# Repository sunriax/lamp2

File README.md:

# WIFI controllable RGB LED lamp

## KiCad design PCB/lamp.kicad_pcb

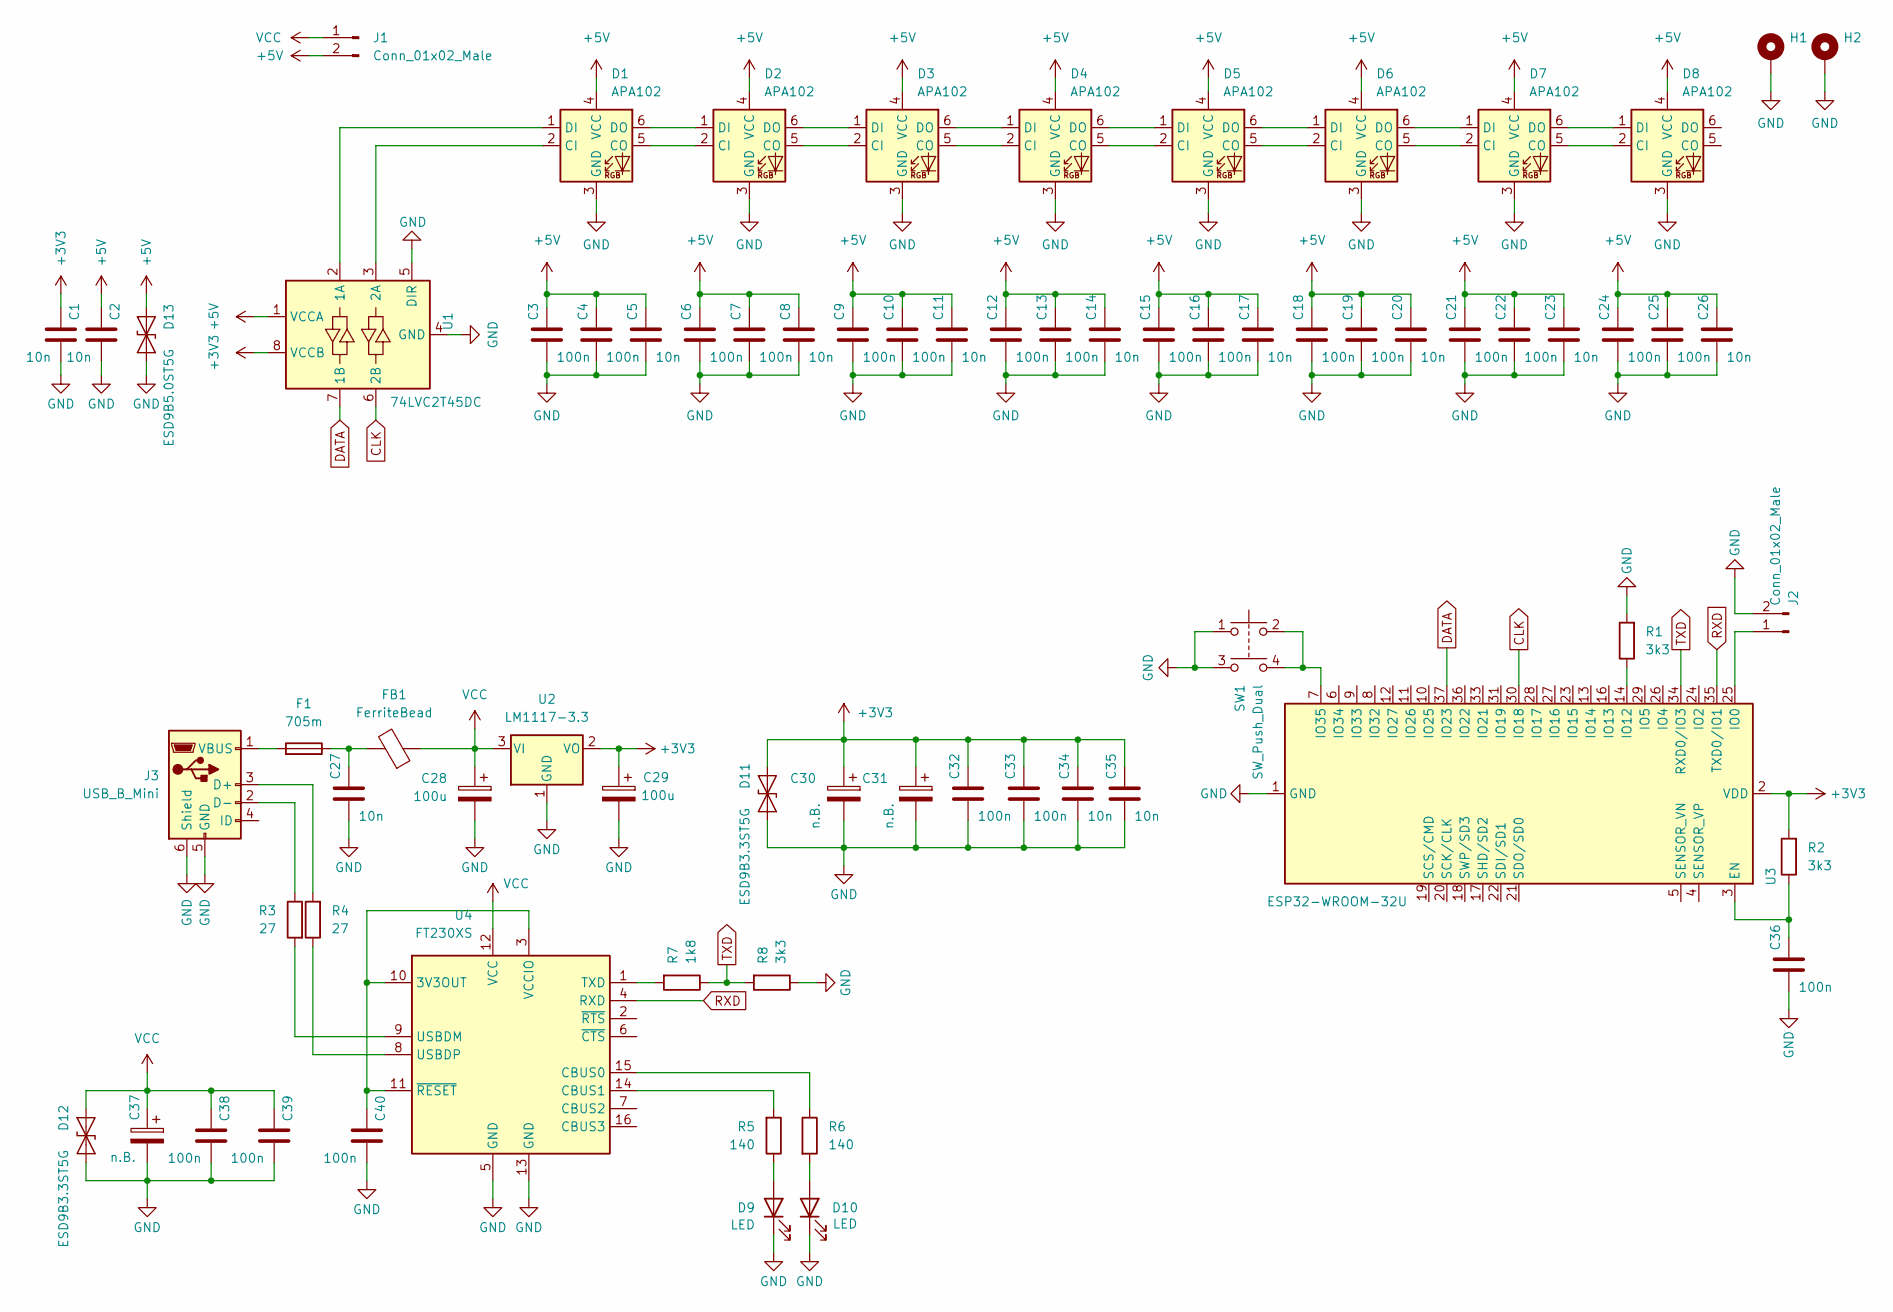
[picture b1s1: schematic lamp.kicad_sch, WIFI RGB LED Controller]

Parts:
C1, C2: 10n; C_0603_1608Metric
C3, C4, C6, C7, C9, C10, C12, C13, C15, C16, C18, C19, C21, C22, C24, C25, C32, C33: 100n; C_1206_3216Metric
C5, C8, C11, C14, C17, C20, C23, C26, C27, C34, C35: 10n; C_1206_3216Metric
C28, C29: 100u; CP_Elec_4x5.8
C30, C31, C37: n.B.; CP_Elec_4x5.8
C36, C38, C39, C40: 100n; C_0603_1608Metric
D1, D2, D3, D4, D5, D6, D7, D8: APA102; LED_RGB_5050-6; DigiKey BL-HBGR32L-3-TRB-8
D9, D10: LED; LED_0603_1608Metric
D11, D12: ESD9B3.3ST5G; D_SOD-923
D13: ESD9B5.0ST5G; D_SOD-923
F1: 705m; Fuse_1210_3225Metric; DigiKey 507-1790-2-ND
FB1: FerriteBead; L_1206_3216Metric; DigiKey 240-2405-2-ND
H1, H2: MountingHole_Pad; MountingHole_2.5mm_Pad
J1, J2: Conn_01x02_Male; PinHeader_1x02_P1.27mm_Horizontal
J3: USB_B_Mini; USB_Mini-B_Wuerth_65100516121_Horizontal; DigiKey 102-4003-2-ND
R1, R2, R8: 3k3; R_0603_1608Metric
R3, R4: 27; R_0603_1608Metric
R5, R6: 140; R_0603_1608Metric
R7: 1k8; R_0603_1608Metric
SW1: SW_Push_Dual; SW_SPST_Omron_B3FS-100xP
U1: 74LVC2T45DC; VSSOP-8_2.3x2mm_P0.5mm
U2: LM1117-3.3; TO-252-2
U3: ESP32-WROOM-32U; DigiKey ESP32-WROOM-32UE-N16
U4: FT230XS; SSOP-16_3.9x4.9mm_P0.635mm; DigiKey 768-1135-6-ND

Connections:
+3V3: C1.1, C29.1, C30.1, C31.1, C32.1, C33.1, C34.1, C35.1, D11.2 (A2), R2.2, U1.8 (VCCB), U2.2 (VO), U3.2 (VDD)
+5V: C2.1, C3.1, C4.1, C5.1, C6.1, C7.1, C8.1, C9.1, C10.1, C11.1, C12.1, C13.1, C14.1, C15.1, C16.1, C17.1, C18.1, C19.1, C20.1, C21.1, C22.1, C23.1, C24.1, C25.1, C26.1, D1.4 (VCC), D2.4 (VCC), D3.4 (VCC), D4.4 (VCC), D5.4 (VCC), D6.4 (VCC), D7.4 (VCC), D8.4 (VCC), D13.2 (A2), J1.2, U1.1 (VCCA)
CLK: U1.6 (2B), U3.30 (IO18)
DATA: U1.7 (1B), U3.37 (IO23)
GND: C1.2, C2.2, C3.2, C4.2, C5.2, C6.2, C7.2, C8.2, C9.2, C10.2, C11.2, C12.2, C13.2, C14.2, C15.2, C16.2, C17.2, C18.2, C19.2, C20.2, C21.2, C22.2, C23.2, C24.2, C25.2, C26.2, C27.2, C28.2, C29.2, C30.2, C31.2, C32.2, C33.2, C34.2, C35.2, C36.2, C37.2, C38.2, C39.2, C40.2, D1.3 (GND), D2.3 (GND), D3.3 (GND), D4.3 (GND), D5.3 (GND), D6.3 (GND), D7.3 (GND), D8.3 (GND), D9.1 (K), D10.1 (K), D11.1 (A1), D12.1 (A1), D13.1 (A1), H1.1, H2.1, J2.2, J3.5 (GND), J3.6 (Shield), R1.2, R8.1, SW1.1, SW1.3, U1.4 (GND), U1.5 (DIR), U2.1 (GND), U3.1 (GND), U3.15 (GND), U3.38 (GND), U3.39 (GND), U4.5 (GND), U4.13 (GND)
unnamed: C27.1, F1.1, FB1.2
unnamed: C36.1, R2.1, U3.3 (EN)
unnamed: C40.1, U4.3 (VCCIO), U4.10 (3V3OUT), U4.11 (~RESET)
unnamed: D1.1 (DI), U1.2 (1A)
unnamed: D1.2 (CI), U1.3 (2A)
unnamed: D1.5 (CO), D2.2 (CI)
unnamed: D1.6 (DO), D2.1 (DI)
unnamed: D2.5 (CO), D3.2 (CI)
unnamed: D2.6 (DO), D3.1 (DI)
unnamed: D3.5 (CO), D4.2 (CI)
unnamed: D3.6 (DO), D4.1 (DI)
unnamed: D4.5 (CO), D5.2 (CI)
unnamed: D4.6 (DO), D5.1 (DI)
unnamed: D5.5 (CO), D6.2 (CI)
unnamed: D5.6 (DO), D6.1 (DI)
unnamed: D6.5 (CO), D7.2 (CI)
unnamed: D6.6 (DO), D7.1 (DI)
unnamed: D7.5 (CO), D8.2 (CI)
unnamed: D7.6 (DO), D8.1 (DI)
unnamed: D9.2 (A), R5.1
unnamed: D10.2 (A), R6.2
unnamed: F1.2, J3.1 (VBUS)
unnamed: J2.1, U3.25 (IO0)
unnamed: J3.2 (D-), R3.1
unnamed: J3.3 (D+), R4.2
unnamed: R1.1, U3.14 (IO12)
unnamed: R3.2, U4.9 (USBDM)
unnamed: R4.1, U4.8 (USBDP)
unnamed: R5.2, U4.14 (CBUS1)
unnamed: R6.1, U4.15 (CBUS0)
unnamed: SW1.2, SW1.4, U3.7 (IO35)
unnamed: R7.2, U4.1 (TXD)
RXD: U3.35 (TXD0/IO1), U4.4 (RXD)
TXD: R7.1, R8.2, U3.34 (RXD0/IO3)
VCC: C28.1, C37.1, C38.1, C39.1, D12.2 (A2), FB1.1, J1.1, U2.3 (VI), U4.12 (VCC)

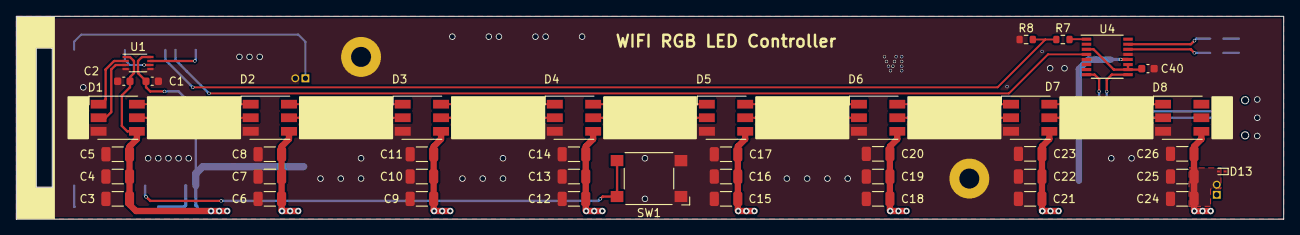
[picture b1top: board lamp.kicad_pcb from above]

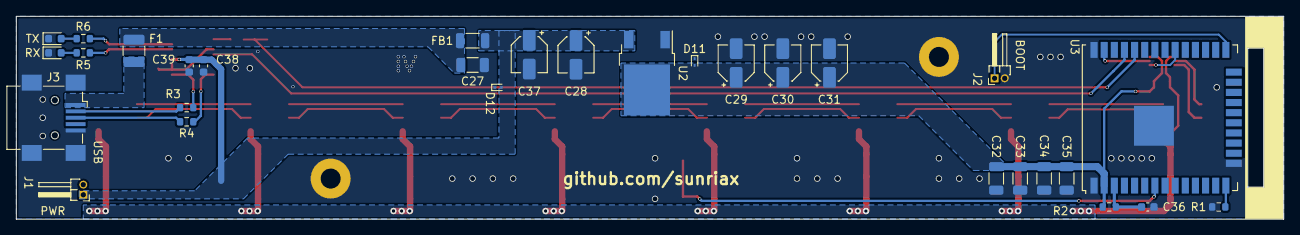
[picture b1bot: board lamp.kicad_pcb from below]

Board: 2 copper layers, 158.8 x 25.4 mm, 73 parts (30 on the bottom side), 40 nets.

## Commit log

2022-03-21 Add pcb design
